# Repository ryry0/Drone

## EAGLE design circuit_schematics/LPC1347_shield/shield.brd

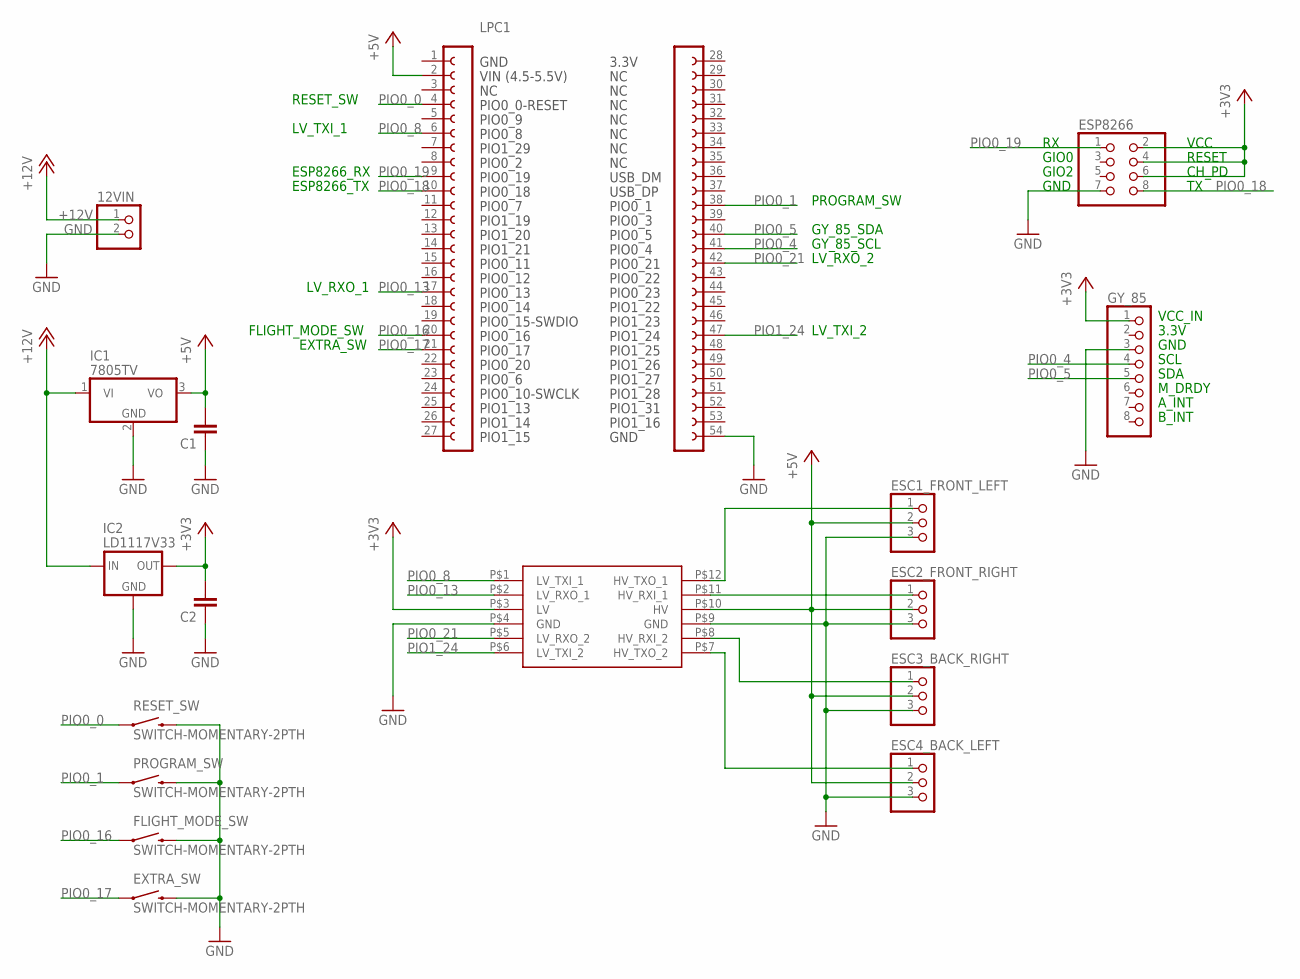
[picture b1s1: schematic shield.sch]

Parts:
12VIN: PINHD-1X2; 1X02
C1, C2: C-EU025-024X044; C025-024X044
ESC1_FRONT_LEFT, ESC2_FRONT_RIGHT, ESC3_BACK_RIGHT, ESC4_BACK_LEFT: PINHD-1X3; 1X03
ESP8266: PINHD-2X4; 2X04
EXTRA_SW: SWITCH-MOMENTARY-2PTH; TACTILE-PTH
FLIGHT_MODE_SW: SWITCH-MOMENTARY-2PTH; TACTILE-PTH
GY_85: PINHD-1X8; 1X08
IC1: 7805TV; TO220V
IC2: LD1117V33
LPC1: LPCXPRESSO_LPC11U14
PROGRAM_SW: SWITCH-MOMENTARY-2PTH; TACTILE-PTH
RESET_SW: SWITCH-MOMENTARY-2PTH; TACTILE-PTH
U$1: LOGIC_LEVEL_CONVERTER

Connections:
+3V3: C2.2, ESP8266.2, ESP8266.4, ESP8266.6, GY_85.1, IC2.OUT, U$1.P$3 (LV)
+5V: C1.2, ESC1_FRONT_LEFT.2, ESC2_FRONT_RIGHT.2, ESC3_BACK_RIGHT.2, ESC4_BACK_LEFT.2, IC1.3 (VO), LPC1.2, U$1.P$10 (HV)
+12V: 12VIN.1, IC1.1 (VI), IC2.IN
GND: 12VIN.2, C1.1, C2.1, ESC1_FRONT_LEFT.3, ESC2_FRONT_RIGHT.3, ESC3_BACK_RIGHT.3, ESC4_BACK_LEFT.3, ESP8266.7, EXTRA_SW.3 (2), FLIGHT_MODE_SW.3 (2), GY_85.3, IC1.2 (GND), IC2.GND, LPC1.54, PROGRAM_SW.3 (2), RESET_SW.3 (2), U$1.P$4 (GND), U$1.P$9 (GND)
unnamed: ESC4_BACK_LEFT.1, U$1.P$7 (HV_TXO_2)
unnamed: ESC3_BACK_RIGHT.1, U$1.P$8 (HV_RXI_2)
unnamed: ESC2_FRONT_RIGHT.1, U$1.P$11 (HV_RXI_1)
unnamed: ESC1_FRONT_LEFT.1, U$1.P$12 (HV_TXO_1)
PIO0_0: LPC1.4, RESET_SW.1
PIO0_1: LPC1.38, PROGRAM_SW.1
PIO0_4: GY_85.4, LPC1.41
PIO0_5: GY_85.5, LPC1.40
PIO0_8: LPC1.6, U$1.P$1 (LV_TXI_1)
PIO0_13: LPC1.17, U$1.P$2 (LV_RXO_1)
PIO0_16: FLIGHT_MODE_SW.1, LPC1.20
PIO0_17: EXTRA_SW.1, LPC1.21
PIO0_18: ESP8266.8, LPC1.10
PIO0_19: ESP8266.1, LPC1.9
PIO0_21: LPC1.42, U$1.P$5 (LV_RXO_2)
PIO1_24: LPC1.47, U$1.P$6 (LV_TXI_2)

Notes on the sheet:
VCC_IN
3.3V
GND
SCL
SDA
M_DRDY
A_INT
B_INT
GIO0
GIO2
VCC
RESET
CH_PD
RESET_SW
LV_TXI_1
ESP8266_TX
LV_RXO_1
FLIGHT_MODE_SW
EXTRA_SW
PROGRAM_SW
GY_85_SDA
GY_85_SCL
LV_RXO_2
LV_TXI_2
ESP8266_RX

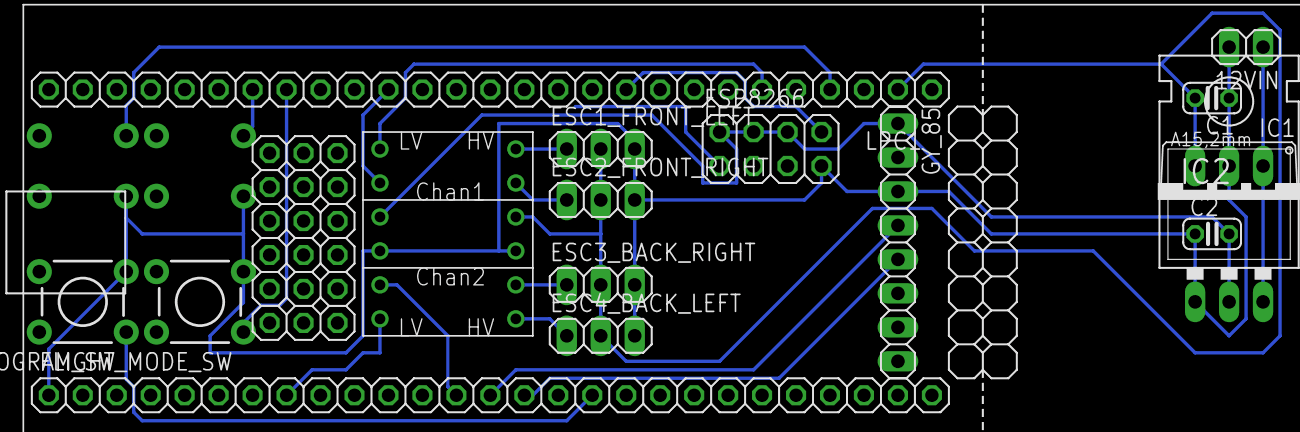
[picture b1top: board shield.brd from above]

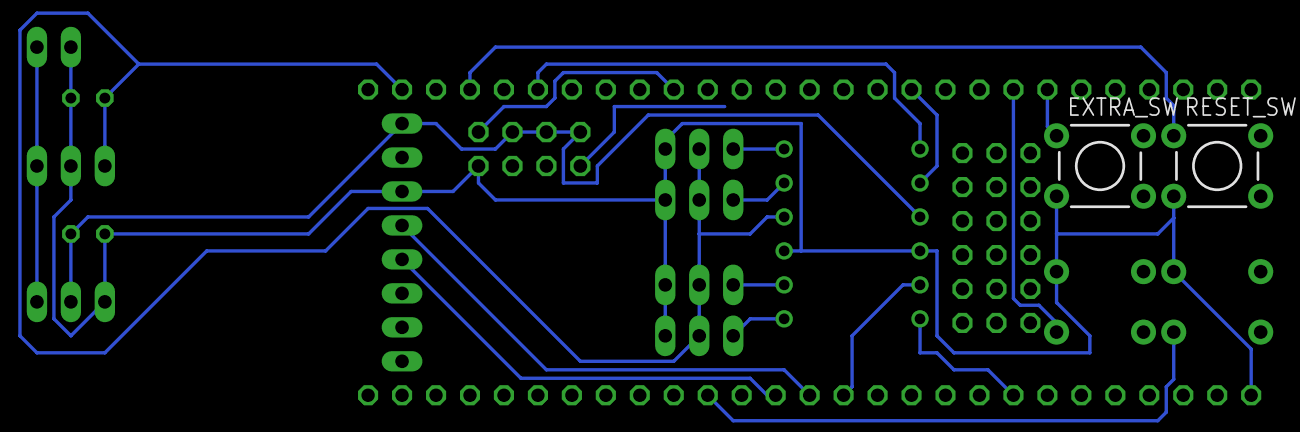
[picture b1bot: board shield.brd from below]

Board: 2 copper layers, 17 parts (2 on the bottom side), 20 nets.

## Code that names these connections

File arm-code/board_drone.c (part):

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  //configure pin0 13 as match output
  LPC_IOCON->TDO_PIO0_13  = PINMODE_CT32B1_MAT0;
  //configure pin0 8
  LPC_IOCON->PIO0_8 = PINMODE_CT16B0_MAT0;
  //configure pin0 21
  LPC_IOCON->PIO0_21 = PINMODE_CT16B1_MAT0;
  //configure pin1 24
  LPC_IOCON->PIO1_24 = PINMODE_CT32B0_MAT0;

  LPC_CT32B0->MCR |= (1 << RESET_MR3);
  LPC_CT32B1->MCR |= (1 << RESET_MR3);
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
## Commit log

2016-03-04 Adding chassis and ESC signaling documents.
2016-03-09 Added ARM board files.
    These require that the microbuilder library be installed two
    folders up, e.g. LIBDIR=../../LPC11U_LPC13U_CodeBase.
2016-03-09 Made the makefile relocatable.
2016-03-14 Testing blink code and digital input code.
2016-03-14 Adc does not really work.
    Configured board_drone.h for printf redirection.
2016-03-15 Systick timer interrupt example.
2016-03-15 Working serial communication.
2016-03-16 Working adc.
2016-03-18 Working gyroscope reading.
2016-03-18 Added gyroscope calibration function.
2016-03-18 Split gyroscope functions into separate files.
2016-03-18 Very noisy accelerometer readings.
    Split accel stuff into separate files.
2016-03-18 Working complementary filter.
    Still kinda acts funny when rotating about multiple axes. There is a lot
    of gyroscope drift. You might want to put software highpass on velocity.
2016-03-18 Renamed gyro data structure elements.
    Changed elements from x,y,z to roll,pitch,yaw so that it has better
    readability.
2016-03-18 Fixed complementary filter implementation.
    Needs to depend on prev filter output not just integrated gyro output.
2016-03-22 Working wifi module.
    The microcontroller is able to listen to a port and accept up to 4
    connections on the port. Will move later on to hosting its own AP.
2016-03-23 Added PID algorithm files.
2016-03-23 Split wifi stuff into extra file; added 4 way pwm.
2016-03-23 Updated PID files to compile.
2016-03-23 Verified that board can generate 4 diff pwm vals.
2016-03-24 Fixed inline function declaration for wifi.
    Moved inline function definition into header file.
2016-03-24 Working float reconstruction.
    Used a union to represent the values of the setpoints for roll, pitch,
    and yaw.
2016-03-25 Created defines for each rotor.
    Mapped rotor names to the counters associated with them.
2016-03-25 Working throttle control over the network.
2016-03-26 Working PID framework.
    Testing PID values on roll axis only, can live tune the PID values over
    the network.
2016-03-28 Tuned filter constant and have PID on all axes.
2016-03-29 Updated integral guard to max at 20% throttle.
2016-03-31 Added ability to updated the D over network.
2016-03-31 Implementation of Fermin's friend's PID.
2016-04-03 Testing integral guard.
    Good values seem to be:
    P: 0.3
    I: 0.001
    D: -0.1?
    Guard: 5000
    Roll: -5.25
2016-04-03 Added yaw correction.
    P: .9 - 1
    I: 0.001 Might go smaller.
    D: -0.2 - -0.3
    Guard 5000
    No pitch or roll correction.
2016-04-19 Updated makefile.
    Makefile now looks for /dev/sda because developing on new laptop.
2016-04-19 Added heartbeat kill timeout.
    If the quadcopter does not receive a packet after 1 second, then it will
    shut off and die.
2016-07-06 Added eagle libraries and shield schematic.
2016-07-07 Finished circuit board with all traces on top layer.
2016-07-07 Moved all traces to back and fixed all errors.
2016-07-10 Hid unnecessary layers.
2016-07-10 Added drill file.
2016-07-10 Added and fixed ground plane for printout.
2016-07-11 Fixed isolation on ground pour.
2016-07-20 Fixed Wiring Error.
    Wire from ESP8266 RX must go to P0_19 not P1_19.
2016-07-25 Changed sendCommand to SendWifiCommand.
2016-07-25 Fixed bug: copter ignored hard kill after delay.
    Copter would go back and put motors to full throttle when hard kill was
    hit and not connected to USB. Serial over USB buffer was filling up and
    causing it to freeze.
    Added extra state which does not print anything and sets all relevant
    variables to zero.
2016-07-25 Fixed makefile to point to /dev/sda. WARNING!!!!
    DO NOT USE MAKEFILE BLINDLY ON NON DELL XPS13 LAPTOPS.
2016-07-30 Interrupt only computes PID when in RUNNING state.
    More efficient compared to computing it all the time.
2016-07-30 Gyro is now diagonal across copter.
    It simplifies the PID algorithm a little bit, making it depend only on
    one of the axes.
2016-08-01 Increased granularity for motor control.
    Increased it by a factor of 10. Now there are 1000 discrete steps
    between 0 throttle and max throttle.
    Did this by decreasing prescaler by a factor of 10. Changed relevant
    defines.
    Added one more byte to throttle variable, so it can go 0 - 1000.
    Now I have to send 27 bytes.
2016-08-03 Prevent PID integral sums from being negative.
    This change led to improved stability. Rotors with 'I' correction
    will only compensate with increased thrust, and will not allow
    the opposite rotor to slow down.
2016-08-04 Fixed bug where only one rotor would have I corrections.
    Constraint was in the wrong place.
2016-08-04 Cleaned up ISR code with less repeated code.
2016-08-04 Cleaned up ISR some more.
    Removed excess PID calculations.
2016-08-05 Implemented new custom PID.
    This PID allows the P term to speed up and slow down rotors.
    However, the I term is clamped to 600 and -throttle.

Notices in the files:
parts and their libraries:
SparkFun-Electromechanical: Licensing: Creative Commons ShareAlike 4.0 International - https://creativecommons.org/licenses/by-sa/4.0
